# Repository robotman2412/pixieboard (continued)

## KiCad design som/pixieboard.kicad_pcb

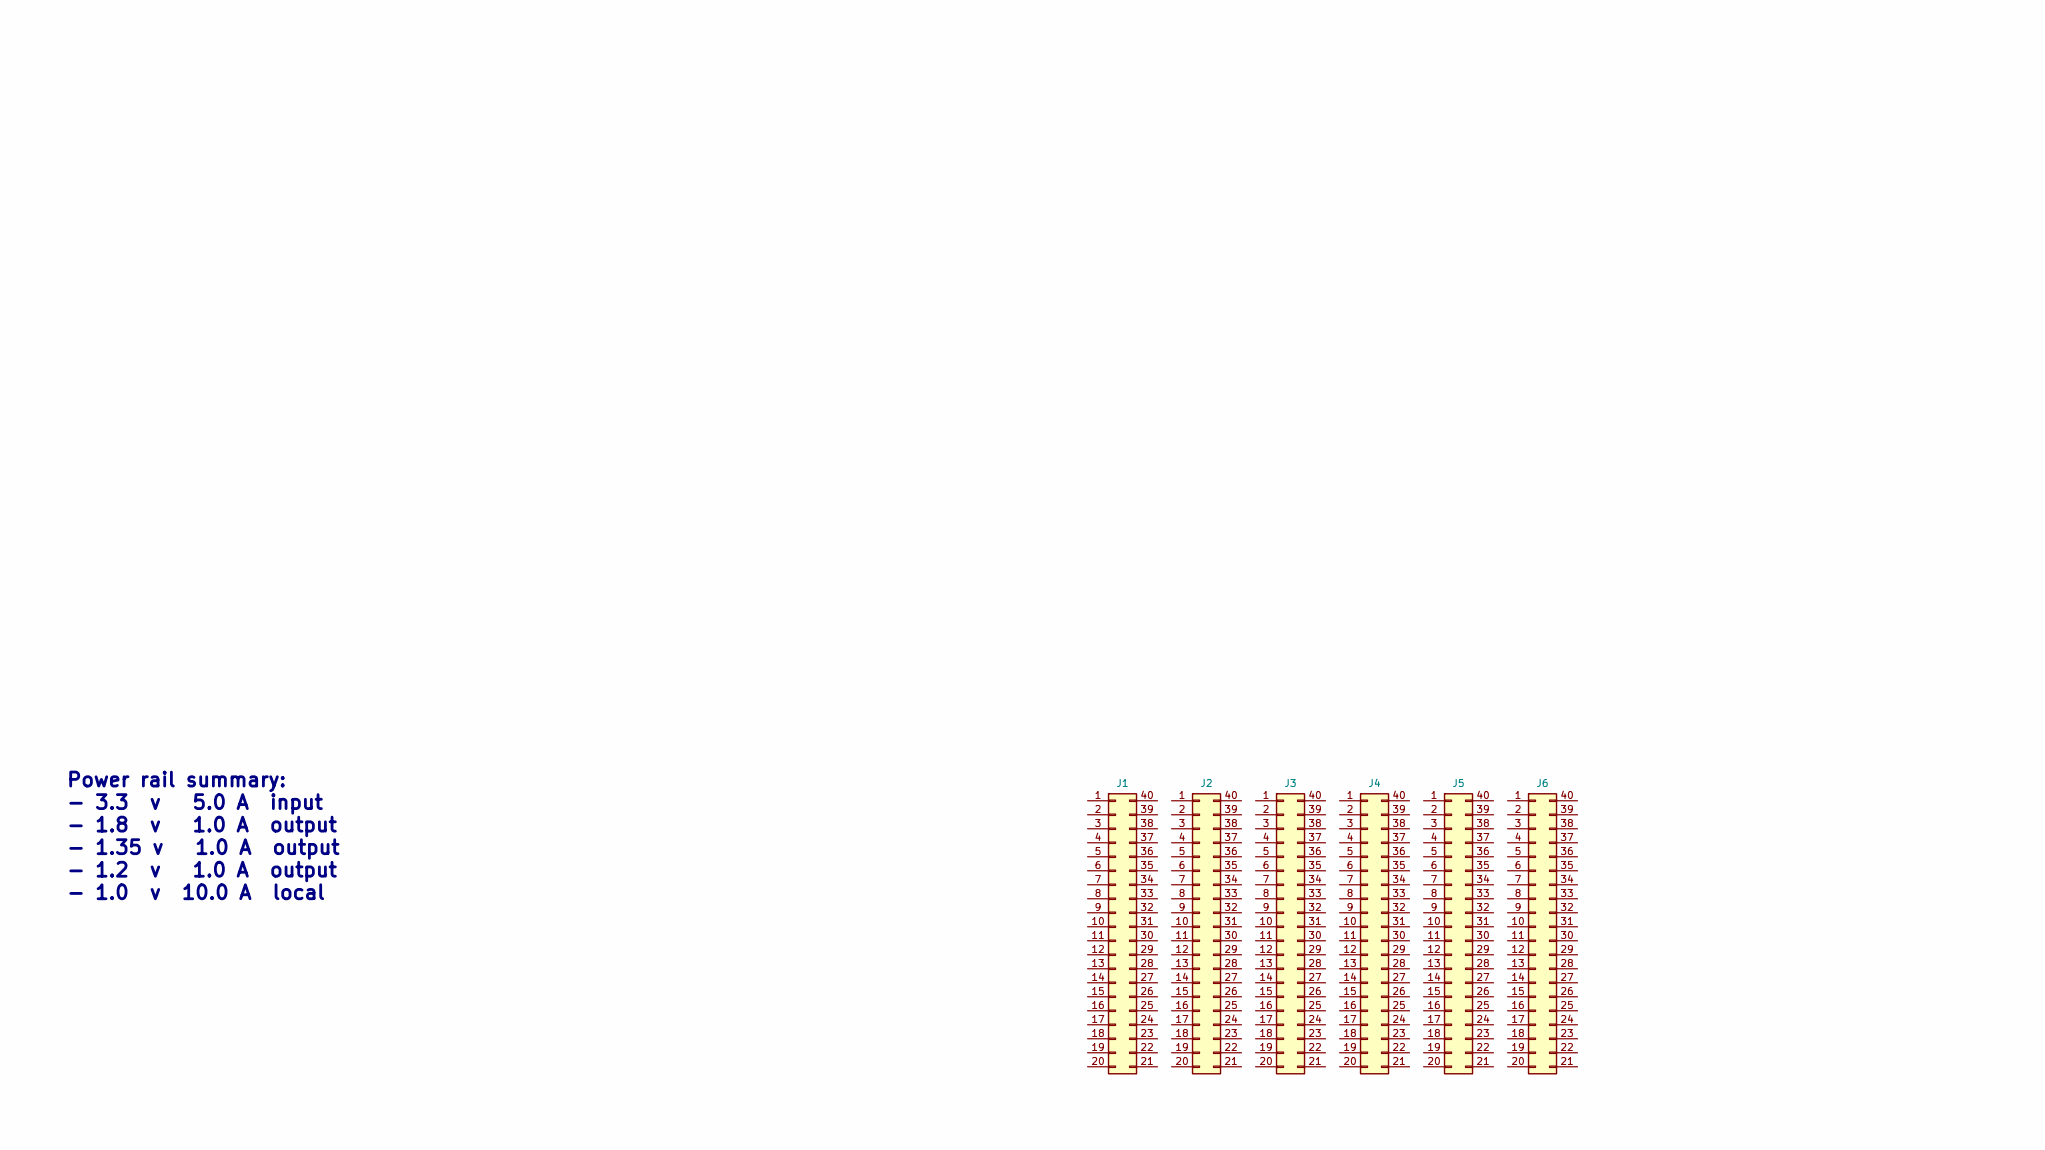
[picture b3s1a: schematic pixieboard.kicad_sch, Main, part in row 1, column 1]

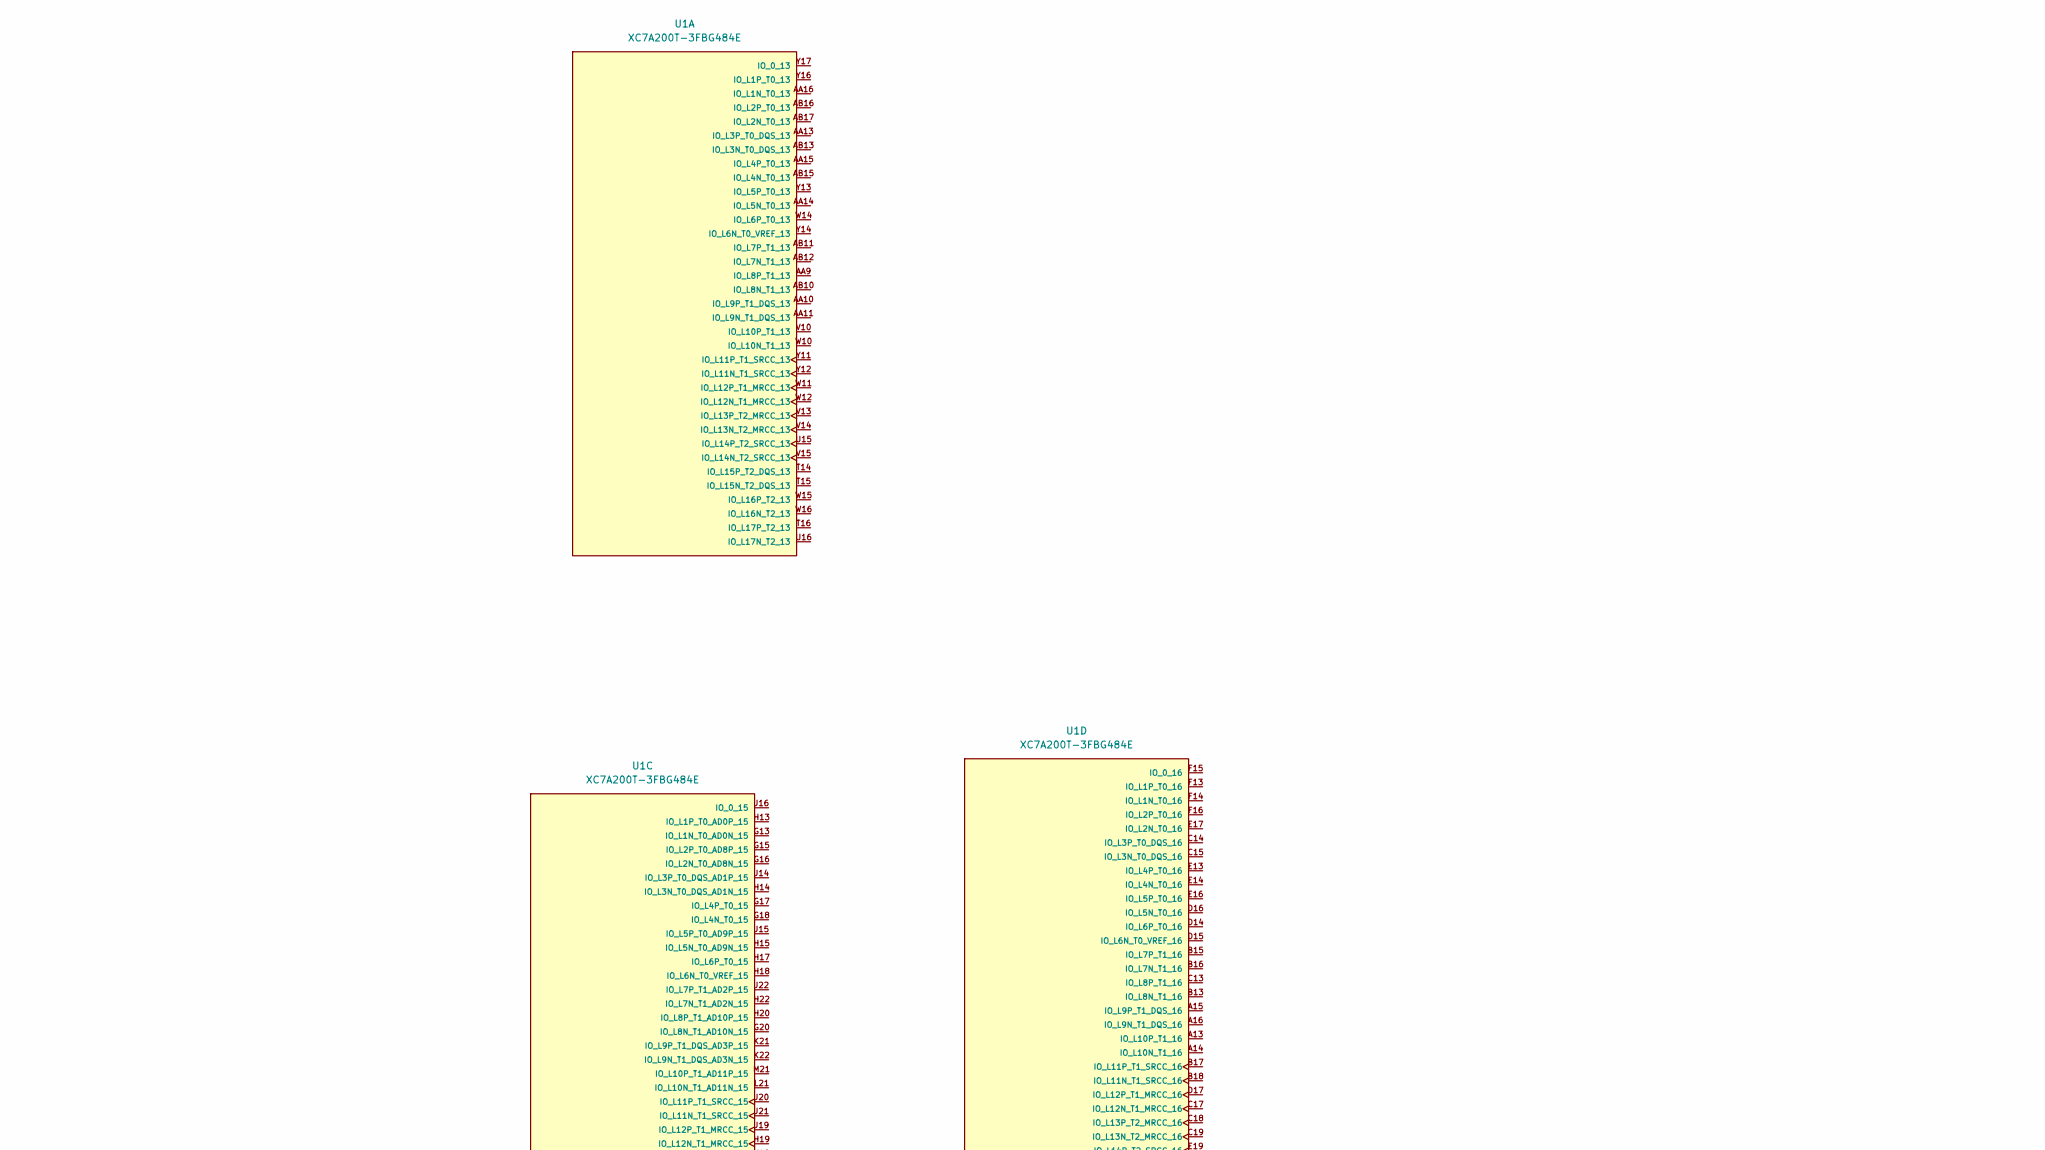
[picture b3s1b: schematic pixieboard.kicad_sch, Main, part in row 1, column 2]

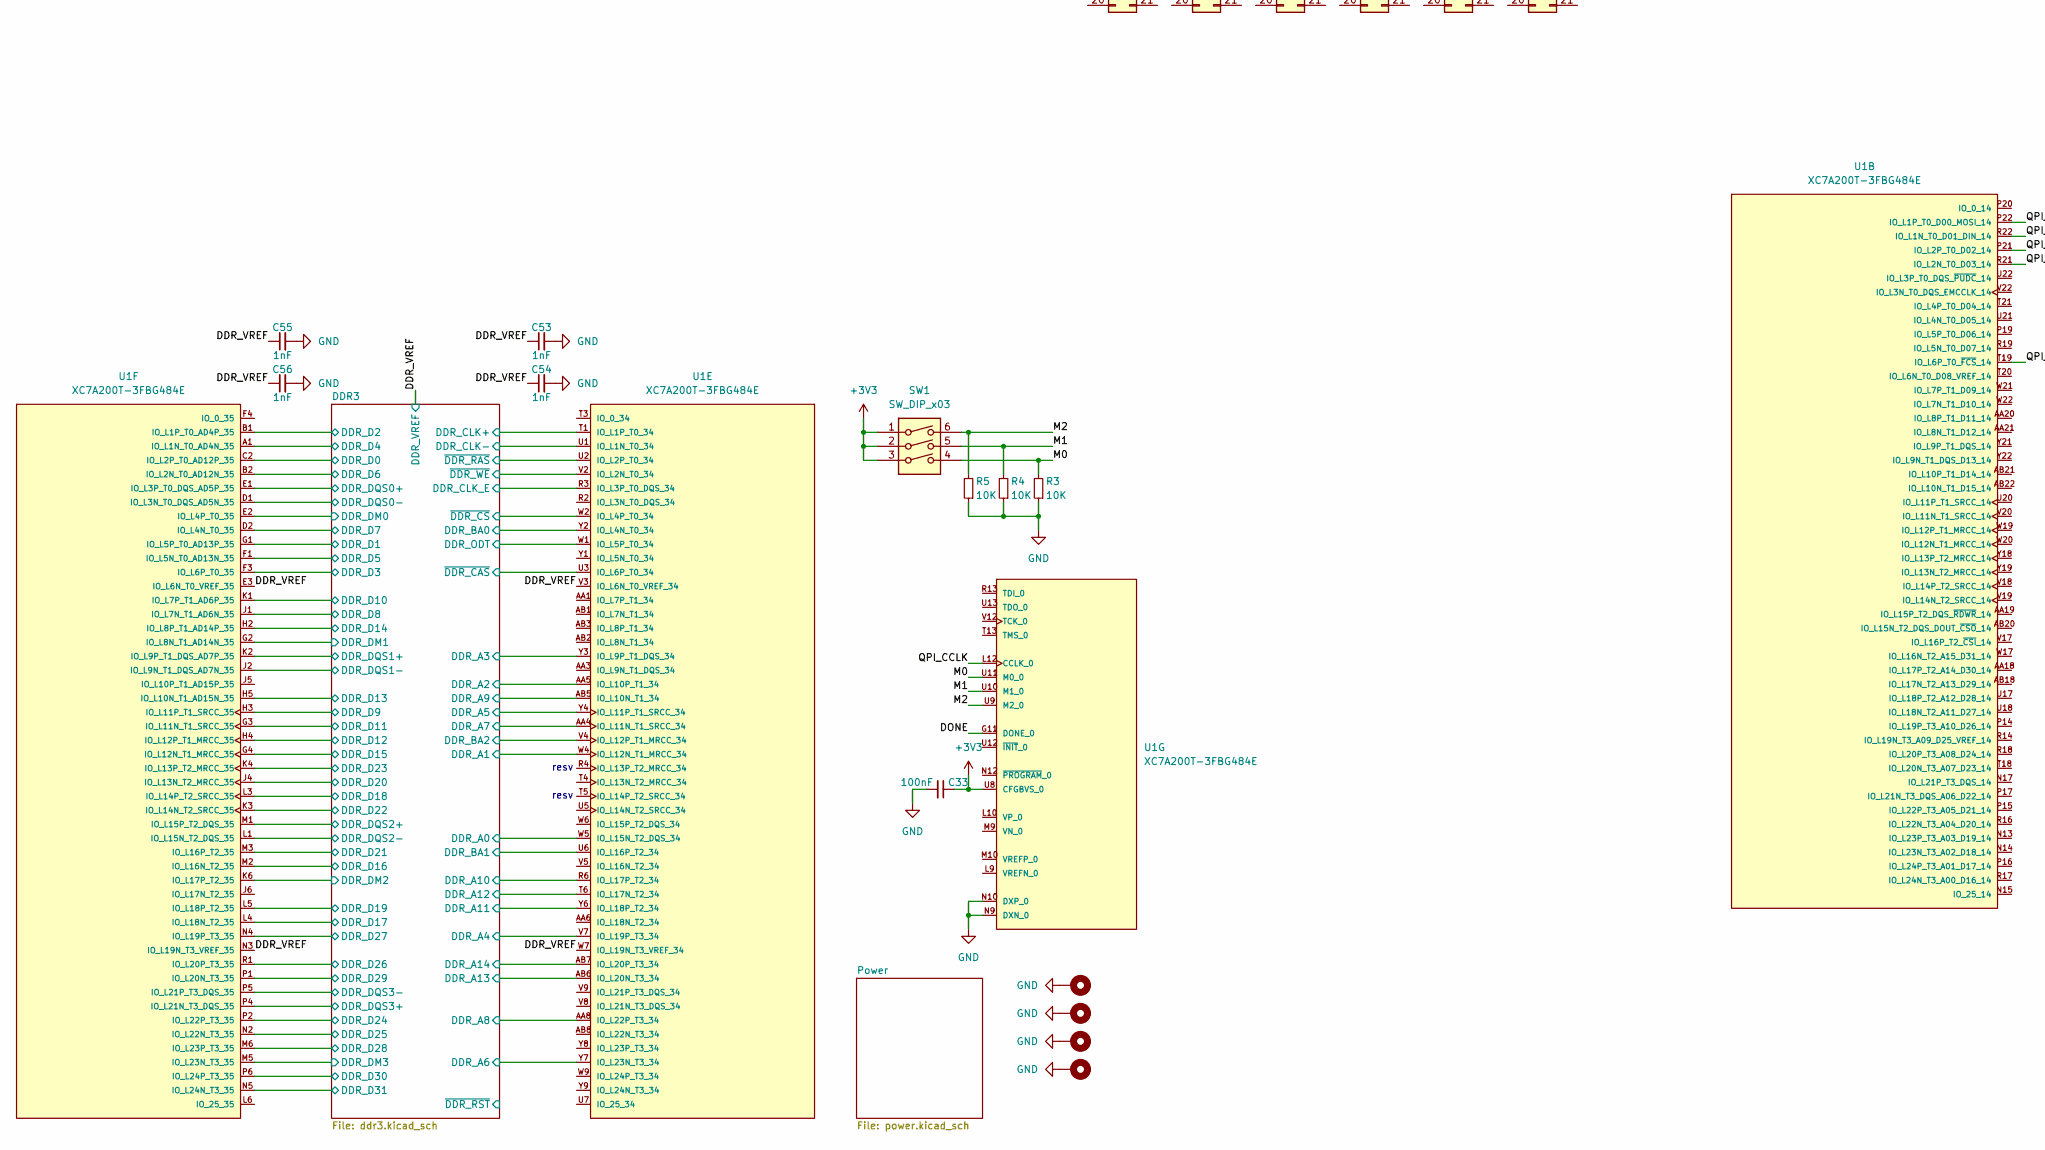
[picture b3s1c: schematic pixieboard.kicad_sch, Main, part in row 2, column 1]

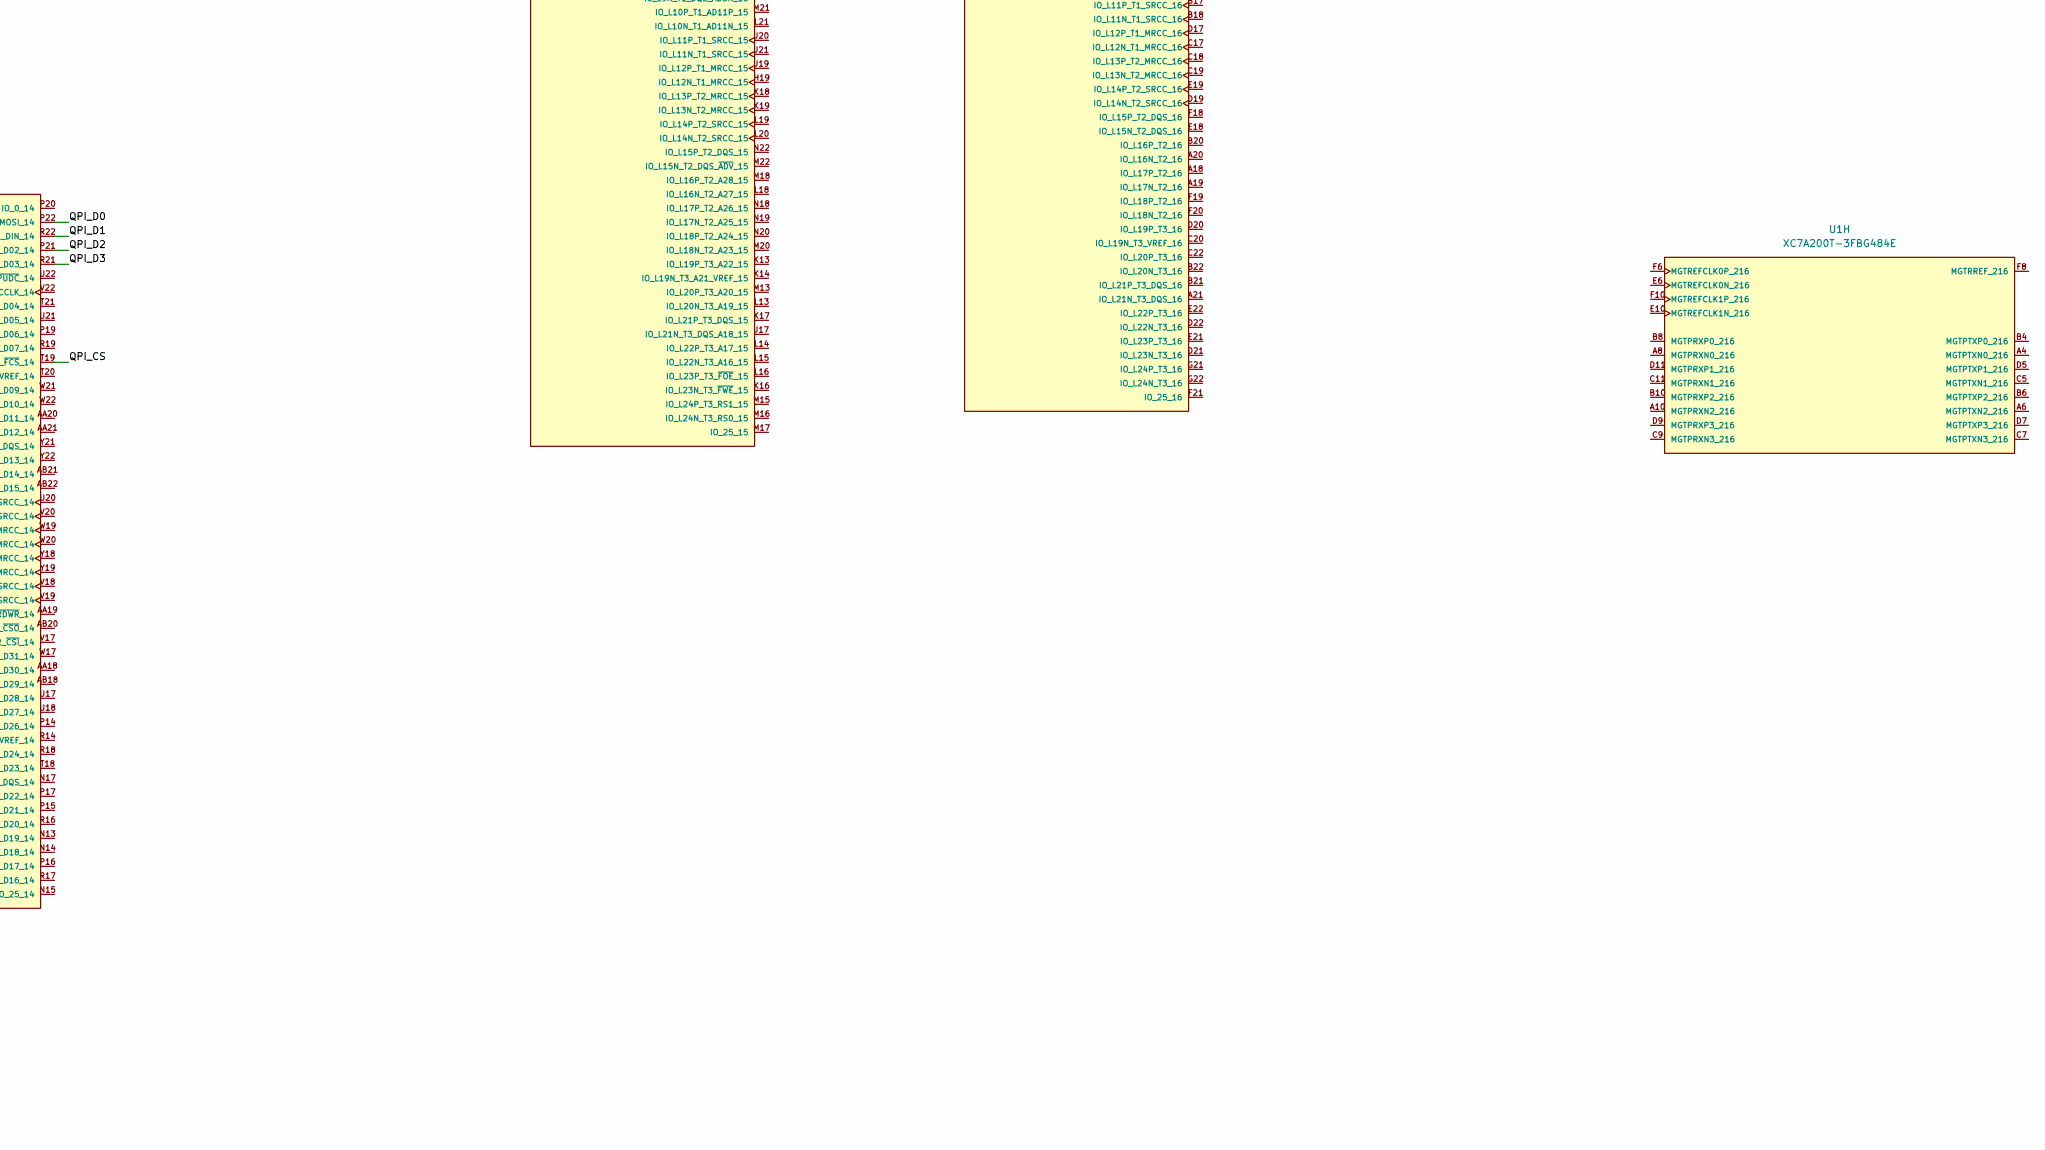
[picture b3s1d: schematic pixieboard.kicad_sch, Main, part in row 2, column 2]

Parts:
C33: 100nF; C_0402_1005Metric
C53, C54, C55, C56: 1nF; C_0402_1005Metric
H1, H2, H3, H4: MountingHole_Pad; MountingHole_2.2mm_M2_DIN965_Pad
J1, J2, J3, J4, J5, J6: Conn_02x20_Counter_Clockwise; Mezz_02x20_p0.5mm_M
R3, R4, R5: 10K; R_0402_1005Metric_Pad0.72x0.64mm_HandSolder
SW1: SW_DIP_x03; SW_DIP_SPSTx03_Slide_Omron_A6S-310x_W8.9mm_P2.54mm
U1: XC7A200T-3FBG484E; Xilinx-XC7A200T-3FBG484E-0-0-MFG; digikey description IC FPGA ARTIX7 285 I/O 484FCBGA

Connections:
+3V3: C33.1, SW1.1, SW1.2, SW1.3, U1.U8 (CFGBVS_0); also elsewhere on the board
/DDR3/DDR_A0: U1.W5 (IO_L15N_T2_DQS_34); also elsewhere on the board
/DDR3/DDR_A1: U1.W4 (IO_L12N_T1_MRCC_34); also elsewhere on the board
/DDR3/DDR_A2: U1.AA5 (IO_L10P_T1_34); also elsewhere on the board
/DDR3/DDR_A3: U1.Y3 (IO_L9P_T1_DQS_34); also elsewhere on the board
/DDR3/DDR_A4: U1.V7 (IO_L19P_T3_34); also elsewhere on the board
/DDR3/DDR_A5: U1.Y4 (IO_L11P_T1_SRCC_34); also elsewhere on the board
/DDR3/DDR_A6: U1.Y7 (IO_L23N_T3_34); also elsewhere on the board
/DDR3/DDR_A7: U1.AA4 (IO_L11N_T1_SRCC_34); also elsewhere on the board
/DDR3/DDR_A8: U1.AA8 (IO_L22P_T3_34); also elsewhere on the board
/DDR3/DDR_A9: U1.AB5 (IO_L10N_T1_34); also elsewhere on the board
/DDR3/DDR_A10: U1.R6 (IO_L17P_T2_34); also elsewhere on the board
/DDR3/DDR_A11: U1.Y6 (IO_L18P_T2_34); also elsewhere on the board
/DDR3/DDR_A12: U1.T6 (IO_L17N_T2_34); also elsewhere on the board
/DDR3/DDR_A13: U1.AB6 (IO_L20N_T3_34); also elsewhere on the board
/DDR3/DDR_A14: U1.AB7 (IO_L20P_T3_34); also elsewhere on the board
/DDR3/DDR_BA0: U1.Y2 (IO_L4N_T0_34); also elsewhere on the board
/DDR3/DDR_BA1: U1.U6 (IO_L16P_T2_34); also elsewhere on the board
/DDR3/DDR_BA2: U1.V4 (IO_L12P_T1_MRCC_34); also elsewhere on the board
/DDR3/DDR_CLK+: U1.T1 (IO_L1P_T0_34); also elsewhere on the board
/DDR3/DDR_CLK-: U1.U1 (IO_L1N_T0_34); also elsewhere on the board
/DDR3/DDR_CLK_E: U1.R3 (IO_L3P_T0_DQS_34); also elsewhere on the board
/DDR3/DDR_D0: U1.C2 (IO_L2P_T0_AD12P_35); also elsewhere on the board
/DDR3/DDR_D1: U1.G1 (IO_L5P_T0_AD13P_35); also elsewhere on the board
/DDR3/DDR_D2: U1.B1 (IO_L1P_T0_AD4P_35); also elsewhere on the board
/DDR3/DDR_D3: U1.F3 (IO_L6P_T0_35); also elsewhere on the board
/DDR3/DDR_D4: U1.A1 (IO_L1N_T0_AD4N_35); also elsewhere on the board
/DDR3/DDR_D5: U1.F1 (IO_L5N_T0_AD13N_35); also elsewhere on the board
/DDR3/DDR_D6: U1.B2 (IO_L2N_T0_AD12N_35); also elsewhere on the board
/DDR3/DDR_D7: U1.D2 (IO_L4N_T0_35); also elsewhere on the board
/DDR3/DDR_D8: U1.J1 (IO_L7N_T1_AD6N_35); also elsewhere on the board
/DDR3/DDR_D9: U1.H3 (IO_L11P_T1_SRCC_35); also elsewhere on the board
/DDR3/DDR_D10: U1.K1 (IO_L7P_T1_AD6P_35); also elsewhere on the board
/DDR3/DDR_D11: U1.G3 (IO_L11N_T1_SRCC_35); also elsewhere on the board
/DDR3/DDR_D12: U1.H4 (IO_L12P_T1_MRCC_35); also elsewhere on the board
/DDR3/DDR_D13: U1.H5 (IO_L10N_T1_AD15N_35); also elsewhere on the board
/DDR3/DDR_D14: U1.H2 (IO_L8P_T1_AD14P_35); also elsewhere on the board
/DDR3/DDR_D15: U1.G4 (IO_L12N_T1_MRCC_35); also elsewhere on the board
/DDR3/DDR_D16: U1.M2 (IO_L16N_T2_35); also elsewhere on the board
/DDR3/DDR_D17: U1.L4 (IO_L18N_T2_35); also elsewhere on the board
/DDR3/DDR_D18: U1.L3 (IO_L14P_T2_SRCC_35); also elsewhere on the board
/DDR3/DDR_D19: U1.L5 (IO_L18P_T2_35); also elsewhere on the board
/DDR3/DDR_D20: U1.J4 (IO_L13N_T2_MRCC_35); also elsewhere on the board
/DDR3/DDR_D21: U1.M3 (IO_L16P_T2_35); also elsewhere on the board
/DDR3/DDR_D22: U1.K3 (IO_L14N_T2_SRCC_35); also elsewhere on the board
/DDR3/DDR_D23: U1.K4 (IO_L13P_T2_MRCC_35); also elsewhere on the board
/DDR3/DDR_D24: U1.P2 (IO_L22P_T3_35); also elsewhere on the board
/DDR3/DDR_D25: U1.N2 (IO_L22N_T3_35); also elsewhere on the board
/DDR3/DDR_D26: U1.R1 (IO_L20P_T3_35); also elsewhere on the board
/DDR3/DDR_D27: U1.N4 (IO_L19P_T3_35); also elsewhere on the board
/DDR3/DDR_D28: U1.M6 (IO_L23P_T3_35); also elsewhere on the board
/DDR3/DDR_D29: U1.P1 (IO_L20N_T3_35); also elsewhere on the board
/DDR3/DDR_D30: U1.P6 (IO_L24P_T3_35); also elsewhere on the board
/DDR3/DDR_D31: U1.N5 (IO_L24N_T3_35); also elsewhere on the board
/DDR3/DDR_DM0: U1.E2 (IO_L4P_T0_35); also elsewhere on the board
/DDR3/DDR_DM1: U1.G2 (IO_L8N_T1_AD14N_35); also elsewhere on the board
/DDR3/DDR_DM2: U1.K6 (IO_L17P_T2_35); also elsewhere on the board
/DDR3/DDR_DM3: U1.M5 (IO_L23N_T3_35); also elsewhere on the board
/DDR3/DDR_DQS0+: U1.E1 (IO_L3P_T0_DQS_AD5P_35); also elsewhere on the board
/DDR3/DDR_DQS0-: U1.D1 (IO_L3N_T0_DQS_AD5N_35); also elsewhere on the board
/DDR3/DDR_DQS1+: U1.K2 (IO_L9P_T1_DQS_AD7P_35); also elsewhere on the board
/DDR3/DDR_DQS1-: U1.J2 (IO_L9N_T1_DQS_AD7N_35); also elsewhere on the board
/DDR3/DDR_DQS2+: U1.M1 (IO_L15P_T2_DQS_35); also elsewhere on the board
/DDR3/DDR_DQS2-: U1.L1 (IO_L15N_T2_DQS_35); also elsewhere on the board
/DDR3/DDR_DQS3+: U1.P4 (IO_L21N_T3_DQS_35); also elsewhere on the board
/DDR3/DDR_DQS3-: U1.P5 (IO_L21P_T3_DQS_35); also elsewhere on the board
/DDR3/DDR_ODT: U1.W1 (IO_L5P_T0_34); also elsewhere on the board
/DDR3/~DDR_CAS: U1.U3 (IO_L6P_T0_34); also elsewhere on the board
/DDR3/~DDR_CS: U1.W2 (IO_L4P_T0_34); also elsewhere on the board
/DDR3/~DDR_RAS: U1.U2 (IO_L2P_T0_34); also elsewhere on the board
/DDR3/~DDR_WE: U1.V2 (IO_L2N_T0_34); also elsewhere on the board
/DDR_VREF: C53.1, C54.1, C55.1, C56.1, U1.E3 (IO_L6N_T0_VREF_35), U1.N3 (IO_L19N_T3_VREF_35), U1.V3 (IO_L6N_T0_VREF_34), U1.W7 (IO_L19N_T3_VREF_34); also elsewhere on the board
/DONE: U1.G11 (DONE_0)
/M0: R3.2, SW1.4, U1.U11 (M0_0)
/M1: R4.2, SW1.5, U1.U10 (M1_0)
/M2: R5.2, SW1.6, U1.U9 (M2_0)
/QPI_CCLK: U1.L12 (CCLK_0)
/QPI_CS: U1.T19 (IO_L6P_T0_~FCS_14)
/QPI_D0: U1.P22 (IO_L1P_T0_D00_MOSI_14)
/QPI_D1: U1.R22 (IO_L1N_T0_D01_DIN_14)
/QPI_D2: U1.P21 (IO_L2P_T0_D02_14)
/QPI_D3: U1.R21 (IO_L2N_T0_D03_14)
GND: C33.2, C53.2, C54.2, C55.2, C56.2, H1.1, H2.1, H3.1, H4.1, R3.1, R4.1, R5.1, U1.N9 (DXN_0), U1.N10 (DXP_0); also elsewhere on the board

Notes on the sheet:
Power rail summary: - 3.3 v 5.0 A input - 1.8 v 1.0 A output - 1.35 v 1.0 A output - 1.2 v 1.0 A output - 1.0 v 10.0 A local
resv

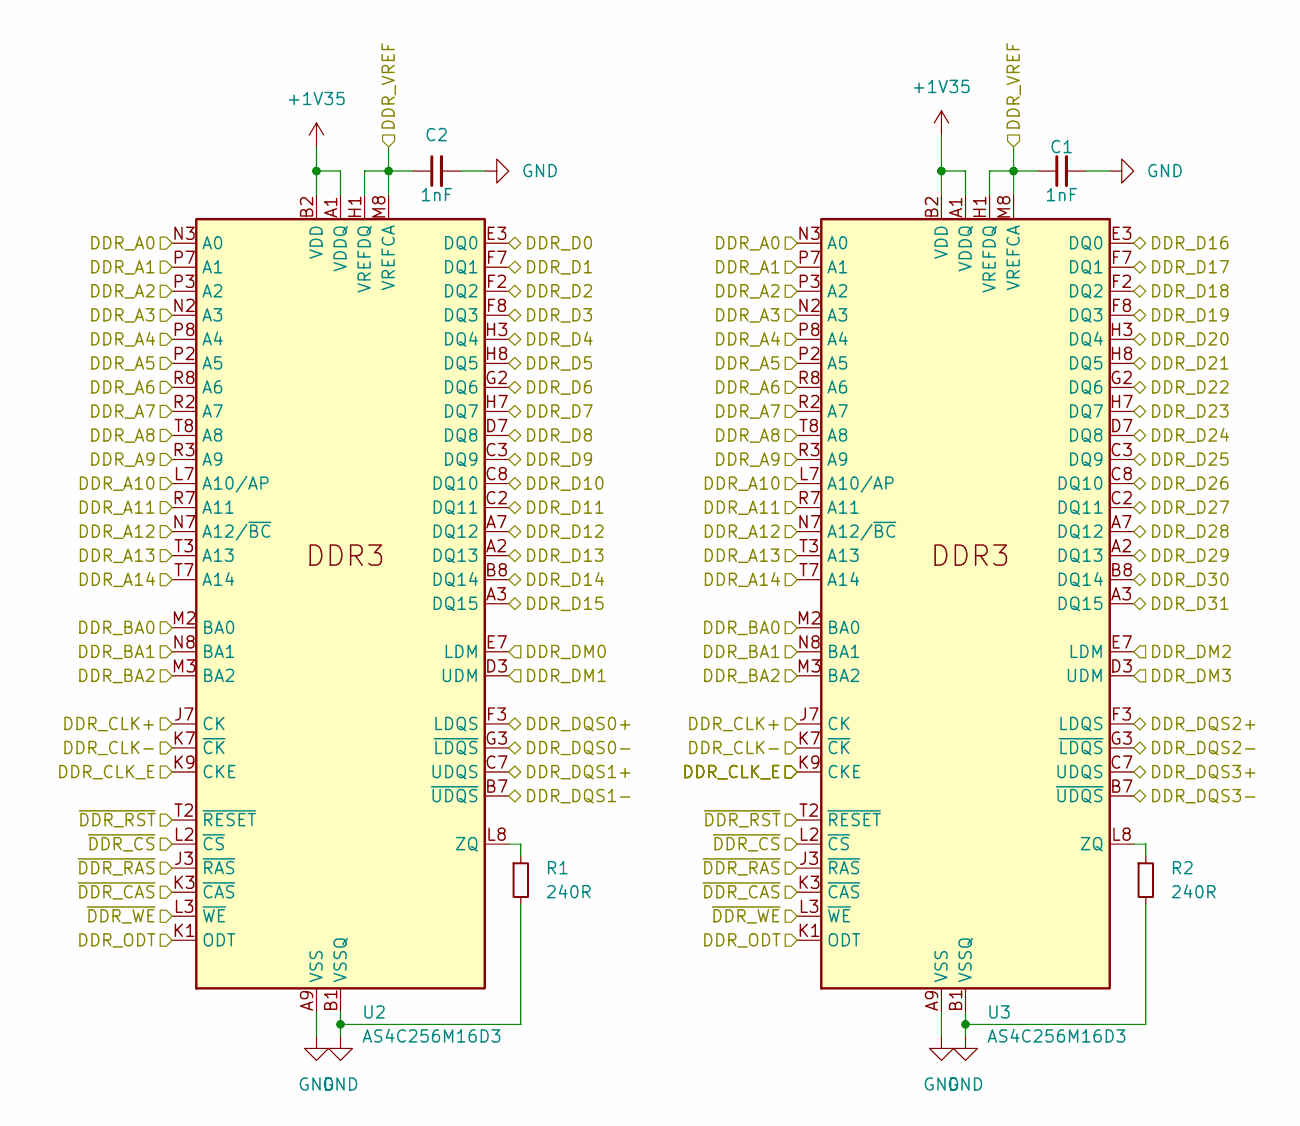
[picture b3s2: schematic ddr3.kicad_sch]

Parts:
C1, C2: 1nF; C_0402_1005Metric
R1, R2: 240R; R_0402_1005Metric_Pad0.72x0.64mm_HandSolder
U2, U3: AS4C256M16D3; BGA-96_9.0x13.0mm_Layout2x3x16_P0.8mm

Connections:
+1V35: U2.A1 (VDDQ), U2.A8 (VDDQ), U2.B2 (VDD), U2.C1 (VDDQ), U2.C9 (VDDQ), U2.D2 (VDDQ), U2.D9 (VDD), U2.E9 (VDDQ), U2.F1 (VDDQ), U2.G7 (VDD), U2.H2 (VDDQ), U2.H9 (VDDQ), U2.K2 (VDD), U2.K8 (VDD), U2.N1 (VDD), U2.N9 (VDD), U2.R1 (VDD), U2.R9 (VDD), U3.A1 (VDDQ), U3.A8 (VDDQ), U3.B2 (VDD), U3.C1 (VDDQ), U3.C9 (VDDQ), U3.D2 (VDDQ), U3.D9 (VDD), U3.E9 (VDDQ), U3.F1 (VDDQ), U3.G7 (VDD), U3.H2 (VDDQ), U3.H9 (VDDQ), U3.K2 (VDD), U3.K8 (VDD), U3.N1 (VDD), U3.N9 (VDD), U3.R1 (VDD), U3.R9 (VDD); also elsewhere on the board
/DDR3/DDR_A0: U2.N3 (A0), U3.N3 (A0); also elsewhere on the board
/DDR3/DDR_A1: U2.P7 (A1), U3.P7 (A1); also elsewhere on the board
/DDR3/DDR_A2: U2.P3 (A2), U3.P3 (A2); also elsewhere on the board
/DDR3/DDR_A3: U2.N2 (A3), U3.N2 (A3); also elsewhere on the board
/DDR3/DDR_A4: U2.P8 (A4), U3.P8 (A4); also elsewhere on the board
/DDR3/DDR_A5: U2.P2 (A5), U3.P2 (A5); also elsewhere on the board
/DDR3/DDR_A6: U2.R8 (A6), U3.R8 (A6); also elsewhere on the board
/DDR3/DDR_A7: U2.R2 (A7), U3.R2 (A7); also elsewhere on the board
/DDR3/DDR_A8: U2.T8 (A8), U3.T8 (A8); also elsewhere on the board
/DDR3/DDR_A9: U2.R3 (A9), U3.R3 (A9); also elsewhere on the board
/DDR3/DDR_A10: U2.L7 (A10/AP), U3.L7 (A10/AP); also elsewhere on the board
/DDR3/DDR_A11: U2.R7 (A11), U3.R7 (A11); also elsewhere on the board
/DDR3/DDR_A12: U2.N7 (A12/~BC), U3.N7 (A12/~BC); also elsewhere on the board
/DDR3/DDR_A13: U2.T3 (A13), U3.T3 (A13); also elsewhere on the board
/DDR3/DDR_A14: U2.T7 (A14), U3.T7 (A14); also elsewhere on the board
/DDR3/DDR_BA0: U2.M2 (BA0), U3.M2 (BA0); also elsewhere on the board
/DDR3/DDR_BA1: U2.N8 (BA1), U3.N8 (BA1); also elsewhere on the board
/DDR3/DDR_BA2: U2.M3 (BA2), U3.M3 (BA2); also elsewhere on the board
/DDR3/DDR_CLK+: U2.J7 (CK), U3.J7 (CK); also elsewhere on the board
/DDR3/DDR_CLK-: U2.K7 (~CK), U3.K7 (~CK); also elsewhere on the board
/DDR3/DDR_CLK_E: U2.K9 (CKE), U3.K9 (CKE); also elsewhere on the board
/DDR3/DDR_D0: U2.E3 (DQ0); also elsewhere on the board
/DDR3/DDR_D1: U2.F7 (DQ1); also elsewhere on the board
/DDR3/DDR_D2: U2.F2 (DQ2); also elsewhere on the board
/DDR3/DDR_D3: U2.F8 (DQ3); also elsewhere on the board
/DDR3/DDR_D4: U2.H3 (DQ4); also elsewhere on the board
/DDR3/DDR_D5: U2.H8 (DQ5); also elsewhere on the board
/DDR3/DDR_D6: U2.G2 (DQ6); also elsewhere on the board
/DDR3/DDR_D7: U2.H7 (DQ7); also elsewhere on the board
/DDR3/DDR_D8: U2.D7 (DQ8); also elsewhere on the board
/DDR3/DDR_D9: U2.C3 (DQ9); also elsewhere on the board
/DDR3/DDR_D10: U2.C8 (DQ10); also elsewhere on the board
/DDR3/DDR_D11: U2.C2 (DQ11); also elsewhere on the board
/DDR3/DDR_D12: U2.A7 (DQ12); also elsewhere on the board
/DDR3/DDR_D13: U2.A2 (DQ13); also elsewhere on the board
/DDR3/DDR_D14: U2.B8 (DQ14); also elsewhere on the board
/DDR3/DDR_D15: U2.A3 (DQ15); also elsewhere on the board
/DDR3/DDR_D16: U3.E3 (DQ0); also elsewhere on the board
/DDR3/DDR_D17: U3.F7 (DQ1); also elsewhere on the board
/DDR3/DDR_D18: U3.F2 (DQ2); also elsewhere on the board
/DDR3/DDR_D19: U3.F8 (DQ3); also elsewhere on the board
/DDR3/DDR_D20: U3.H3 (DQ4); also elsewhere on the board
/DDR3/DDR_D21: U3.H8 (DQ5); also elsewhere on the board
/DDR3/DDR_D22: U3.G2 (DQ6); also elsewhere on the board
/DDR3/DDR_D23: U3.H7 (DQ7); also elsewhere on the board
/DDR3/DDR_D24: U3.D7 (DQ8); also elsewhere on the board
/DDR3/DDR_D25: U3.C3 (DQ9); also elsewhere on the board
/DDR3/DDR_D26: U3.C8 (DQ10); also elsewhere on the board
/DDR3/DDR_D27: U3.C2 (DQ11); also elsewhere on the board
/DDR3/DDR_D28: U3.A7 (DQ12); also elsewhere on the board
/DDR3/DDR_D29: U3.A2 (DQ13); also elsewhere on the board
/DDR3/DDR_D30: U3.B8 (DQ14); also elsewhere on the board
/DDR3/DDR_D31: U3.A3 (DQ15); also elsewhere on the board
/DDR3/DDR_DM0: U2.E7 (LDM); also elsewhere on the board
/DDR3/DDR_DM1: U2.D3 (UDM); also elsewhere on the board
/DDR3/DDR_DM2: U3.E7 (LDM); also elsewhere on the board
/DDR3/DDR_DM3: U3.D3 (UDM); also elsewhere on the board
/DDR3/DDR_DQS0+: U2.F3 (LDQS); also elsewhere on the board
/DDR3/DDR_DQS0-: U2.G3 (~LDQS); also elsewhere on the board
/DDR3/DDR_DQS1+: U2.C7 (UDQS); also elsewhere on the board
/DDR3/DDR_DQS1-: U2.B7 (~UDQS); also elsewhere on the board
/DDR3/DDR_DQS2+: U3.F3 (LDQS); also elsewhere on the board
/DDR3/DDR_DQS2-: U3.G3 (~LDQS); also elsewhere on the board
/DDR3/DDR_DQS3+: U3.C7 (UDQS); also elsewhere on the board
/DDR3/DDR_DQS3-: U3.B7 (~UDQS); also elsewhere on the board
/DDR3/DDR_ODT: U2.K1 (ODT), U3.K1 (ODT); also elsewhere on the board
/DDR3/~DDR_CAS: U2.K3 (~CAS), U3.K3 (~CAS); also elsewhere on the board
/DDR3/~DDR_CS: U2.L2 (~CS), U3.L2 (~CS); also elsewhere on the board
/DDR3/~DDR_RAS: U2.J3 (~RAS), U3.J3 (~RAS); also elsewhere on the board
/DDR3/~DDR_RST: U2.T2 (~RESET), U3.T2 (~RESET)
/DDR3/~DDR_WE: U2.L3 (~WE), U3.L3 (~WE); also elsewhere on the board
/DDR_VREF: C1.1, C2.1, U2.H1 (VREFDQ), U2.M8 (VREFCA), U3.H1 (VREFDQ), U3.M8 (VREFCA); also elsewhere on the board
GND: C1.2, C2.2, R1.2, R2.2, U2.A9 (VSS), U2.B1 (VSSQ), U2.B3 (VSS), U2.B9 (VSSQ), U2.D1 (VSSQ), U2.D8 (VSSQ), U2.E1 (VSS), U2.E2 (VSSQ), U2.E8 (VSSQ), U2.F9 (VSSQ), U2.G1 (VSSQ), U2.G8 (VSS), U2.G9 (VSSQ), U2.J2 (VSS), U2.J8 (VSS), U2.M1 (VSS), U2.M9 (VSS), U2.P1 (VSS), U2.P9 (VSS), U2.T1 (VSS), U2.T9 (VSS), U3.A9 (VSS), U3.B1 (VSSQ), U3.B3 (VSS), U3.B9 (VSSQ), U3.D1 (VSSQ), U3.D8 (VSSQ), U3.E1 (VSS), U3.E2 (VSSQ), U3.E8 (VSSQ), U3.F9 (VSSQ), U3.G1 (VSSQ), U3.G8 (VSS), U3.G9 (VSSQ), U3.J2 (VSS), U3.J8 (VSS), U3.M1 (VSS), U3.M9 (VSS), U3.P1 (VSS), U3.P9 (VSS), U3.T1 (VSS), U3.T9 (VSS); also elsewhere on the board
unnamed: R1.1, U2.L8 (ZQ)
unnamed: R2.1, U3.L8 (ZQ)

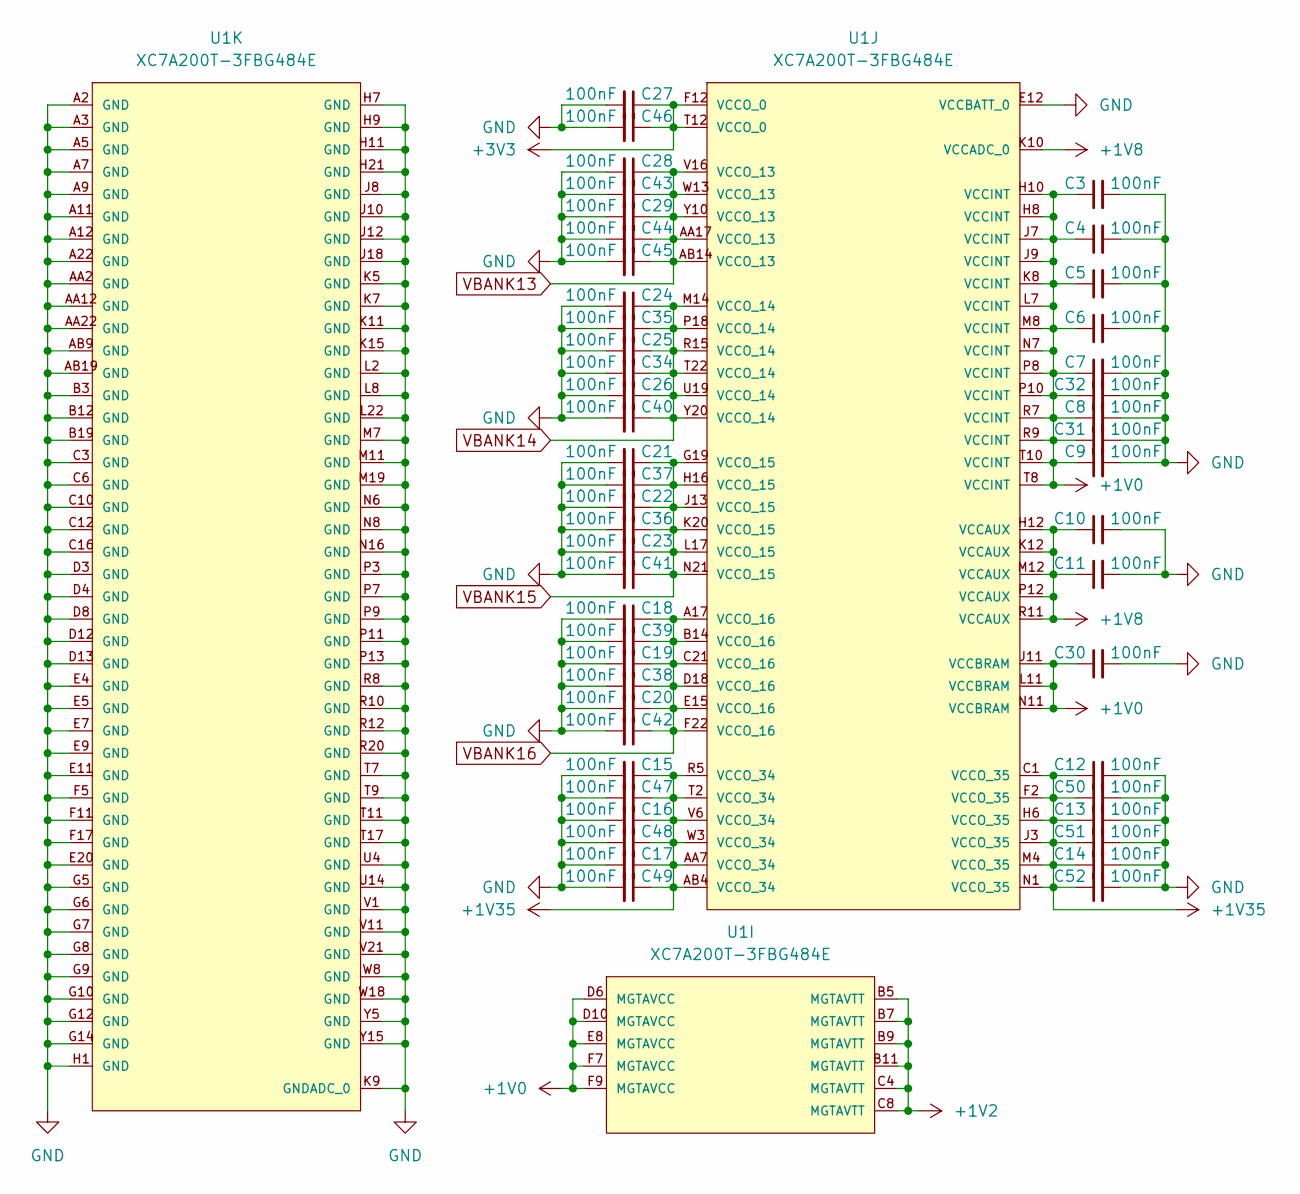
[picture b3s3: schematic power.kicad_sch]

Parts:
C3, C4, C5, C6, C7, C8, C9, C10, C11, C12, C13, C14, C15, C16, C17, C18, C19, C20, C21, C22, C23, C24, C25, C26, C27, C28, C29, C30, C31, C32, C34, C35, C36, C37, C38, C39, C40, C41, C42, C43, C44, C45, C46, C47, C48, C49, C50, C51, C52: 100nF; C_0402_1005Metric
U1: XC7A200T-3FBG484E; Xilinx-XC7A200T-3FBG484E-0-0-MFG; digikey description IC FPGA ARTIX7 285 I/O 484FCBGA

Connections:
+1V0: C3.1, C4.1, C5.1, C6.1, C7.1, C8.1, C9.1, C30.1, C31.1, C32.1, U1.D6 (MGTAVCC), U1.D10 (MGTAVCC), U1.E8 (MGTAVCC), U1.F7 (MGTAVCC), U1.F9 (MGTAVCC), U1.H8 (VCCINT), U1.H10 (VCCINT), U1.J7 (VCCINT), U1.J9 (VCCINT), U1.J11 (VCCBRAM), U1.K8 (VCCINT), U1.L7 (VCCINT), U1.L11 (VCCBRAM), U1.M8 (VCCINT), U1.N7 (VCCINT), U1.N11 (VCCBRAM), U1.P8 (VCCINT), U1.P10 (VCCINT), U1.R7 (VCCINT), U1.R9 (VCCINT), U1.T8 (VCCINT), U1.T10 (VCCINT)
+1V2: U1.B5 (MGTAVTT), U1.B7 (MGTAVTT), U1.B9 (MGTAVTT), U1.B11 (MGTAVTT), U1.C4 (MGTAVTT), U1.C8 (MGTAVTT)
+1V8: C10.1, C11.1, U1.H12 (VCCAUX), U1.K10 (VCCADC_0), U1.K12 (VCCAUX), U1.M12 (VCCAUX), U1.P12 (VCCAUX), U1.R11 (VCCAUX)
+1V35: C12.1, C13.1, C14.1, C15.1, C16.1, C17.1, C47.1, C48.1, C49.1, C50.1, C51.1, C52.1, U1.AA7 (VCCO_34), U1.AB4 (VCCO_34), U1.C1 (VCCO_35), U1.F2 (VCCO_35), U1.H6 (VCCO_35), U1.J3 (VCCO_35), U1.M4 (VCCO_35), U1.N1 (VCCO_35), U1.R5 (VCCO_34), U1.T2 (VCCO_34), U1.V6 (VCCO_34), U1.W3 (VCCO_34); also elsewhere on the board
+3V3: C27.1, C46.1, U1.F12 (VCCO_0), U1.T12 (VCCO_0); also elsewhere on the board
GND: C3.2, C4.2, C5.2, C6.2, C7.2, C8.2, C9.2, C10.2, C11.2, C12.2, C13.2, C14.2, C15.2, C16.2, C17.2, C18.2, C19.2, C20.2, C21.2, C22.2, C23.2, C24.2, C25.2, C26.2, C27.2, C28.2, C29.2, C30.2, C31.2, C32.2, C34.2, C35.2, C36.2, C37.2, C38.2, C39.2, C40.2, C41.2, C42.2, C43.2, C44.2, C45.2, C46.2, C47.2, C48.2, C49.2, C50.2, C51.2, C52.2, U1.A2 (GND), U1.A3 (GND), U1.A5 (GND), U1.A7 (GND), U1.A9 (GND), U1.A11 (GND), U1.A12 (GND), U1.A22 (GND), U1.AA2 (GND), U1.AA12 (GND), U1.AA22 (GND), U1.AB9 (GND), U1.AB19 (GND), U1.B3 (GND), U1.B12 (GND), U1.B19 (GND), U1.C3 (GND), U1.C6 (GND), U1.C10 (GND), U1.C12 (GND), U1.C16 (GND), U1.D3 (GND), U1.D4 (GND), U1.D8 (GND), U1.D12 (GND), U1.D13 (GND), U1.E4 (GND), U1.E5 (GND), U1.E7 (GND), U1.E9 (GND), U1.E11 (GND), U1.E12 (VCCBATT_0), U1.E20 (GND), U1.F5 (GND), U1.F11 (GND), U1.F17 (GND), U1.G5 (GND), U1.G6 (GND), U1.G7 (GND), U1.G8 (GND), U1.G9 (GND), U1.G10 (GND), U1.G12 (GND), U1.G14 (GND), U1.H1 (GND), U1.H7 (GND), U1.H9 (GND), U1.H11 (GND), U1.H21 (GND), U1.J8 (GND), U1.J10 (GND), U1.J12 (GND), U1.J18 (GND), U1.K5 (GND), U1.K7 (GND), U1.K9 (GNDADC_0), U1.K11 (GND), U1.K15 (GND), U1.L2 (GND), U1.L8 (GND), U1.L22 (GND), U1.M7 (GND), U1.M11 (GND), U1.M19 (GND), U1.N6 (GND), U1.N8 (GND), U1.N16 (GND), U1.P3 (GND), U1.P7 (GND), U1.P9 (GND), U1.P11 (GND), U1.P13 (GND), U1.R8 (GND), U1.R10 (GND), U1.R12 (GND), U1.R20 (GND), U1.T7 (GND), U1.T9 (GND), U1.T11 (GND), U1.T17 (GND), U1.U4 (GND), U1.U14 (GND), U1.V1 (GND), U1.V11 (GND), U1.V21 (GND), U1.W8 (GND), U1.W18 (GND), U1.Y5 (GND), U1.Y15 (GND); also elsewhere on the board
VBANK13: C28.1, C29.1, C43.1, C44.1, C45.1, U1.AA17 (VCCO_13), U1.AB14 (VCCO_13), U1.V16 (VCCO_13), U1.W13 (VCCO_13), U1.Y10 (VCCO_13)
VBANK14: C24.1, C25.1, C26.1, C34.1, C35.1, C40.1, U1.M14 (VCCO_14), U1.P18 (VCCO_14), U1.R15 (VCCO_14), U1.T22 (VCCO_14), U1.U19 (VCCO_14), U1.Y20 (VCCO_14)
VBANK15: C21.1, C22.1, C23.1, C36.1, C37.1, C41.1, U1.G19 (VCCO_15), U1.H16 (VCCO_15), U1.J13 (VCCO_15), U1.K20 (VCCO_15), U1.L17 (VCCO_15), U1.N21 (VCCO_15)
VBANK16: C18.1, C19.1, C20.1, C38.1, C39.1, C42.1, U1.A17 (VCCO_16), U1.B14 (VCCO_16), U1.C21 (VCCO_16), U1.D18 (VCCO_16), U1.E15 (VCCO_16), U1.F22 (VCCO_16)
